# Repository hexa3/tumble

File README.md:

# tumble

its a dice but the pips act like real little discs. tilt it and they roll around, shake it and they bounce off the walls. when u stop shaking it picks a random number, the pips jump into that face and a motor goes thud.

it does d4, d6, d8, d10, d12, d20 and d100. double tap the face to switch.

tumble is the sequel to tinydie mk i (an attiny412 with 7 leds on a coin cell). when it turns on the pips start in the mk i's "7" pattern, and theres a gold outline of the old chip on the back cuz i love that little guy.

## whats inside

its 3 boards stacked up, 50x50mm each:

- **face**: 121 tiny leds in an 11x11 grid, run by an is31fl3733b
- **core**: the brain. an 8 pin stm32g041j6, a lis3dh accelerometer, a drv2605l with a buzzy motor, and an avalanche noise thing for randomness
- **base**: usb-c, battery charging, an mcp2221a for usb serial, a max17048 battery gauge and the battery

## is it actually fair

ya and u can check it urself. the noise goes through health tests (sp 800-90b) so it cant be stuck, then gets mixed into a blake2s pool that feeds chacha20, and the rolls come out of that. if the noise thing dies it switches to the chips own random generator and a little dot shows up in the corner.

plug it into usb and open serial at 115200:

```
raw N       dumps N raw noise samples
roll N S    rolls an S sided die N times, reseeding before each one
health      shows if the noise is ok
```

## building it

**firmware** (`firmware/`): its platformio. the so-8 chip isnt in platformio so theres my own board file in `boards/tumble_g041j6.json`. heads up: the debug pins turn into other stuff after boot, so u only have 2 seconds after reset to plug in a programmer.

**boards** (`hardware/`): run `build.sh`. it makes all 3 boards, runs drc (stops if anything fails), and spits out gerbers, boms, jlc files and pictures into `hardware/release/`. u need kicad 10 and the system python.

## what i still need to do

build it :)

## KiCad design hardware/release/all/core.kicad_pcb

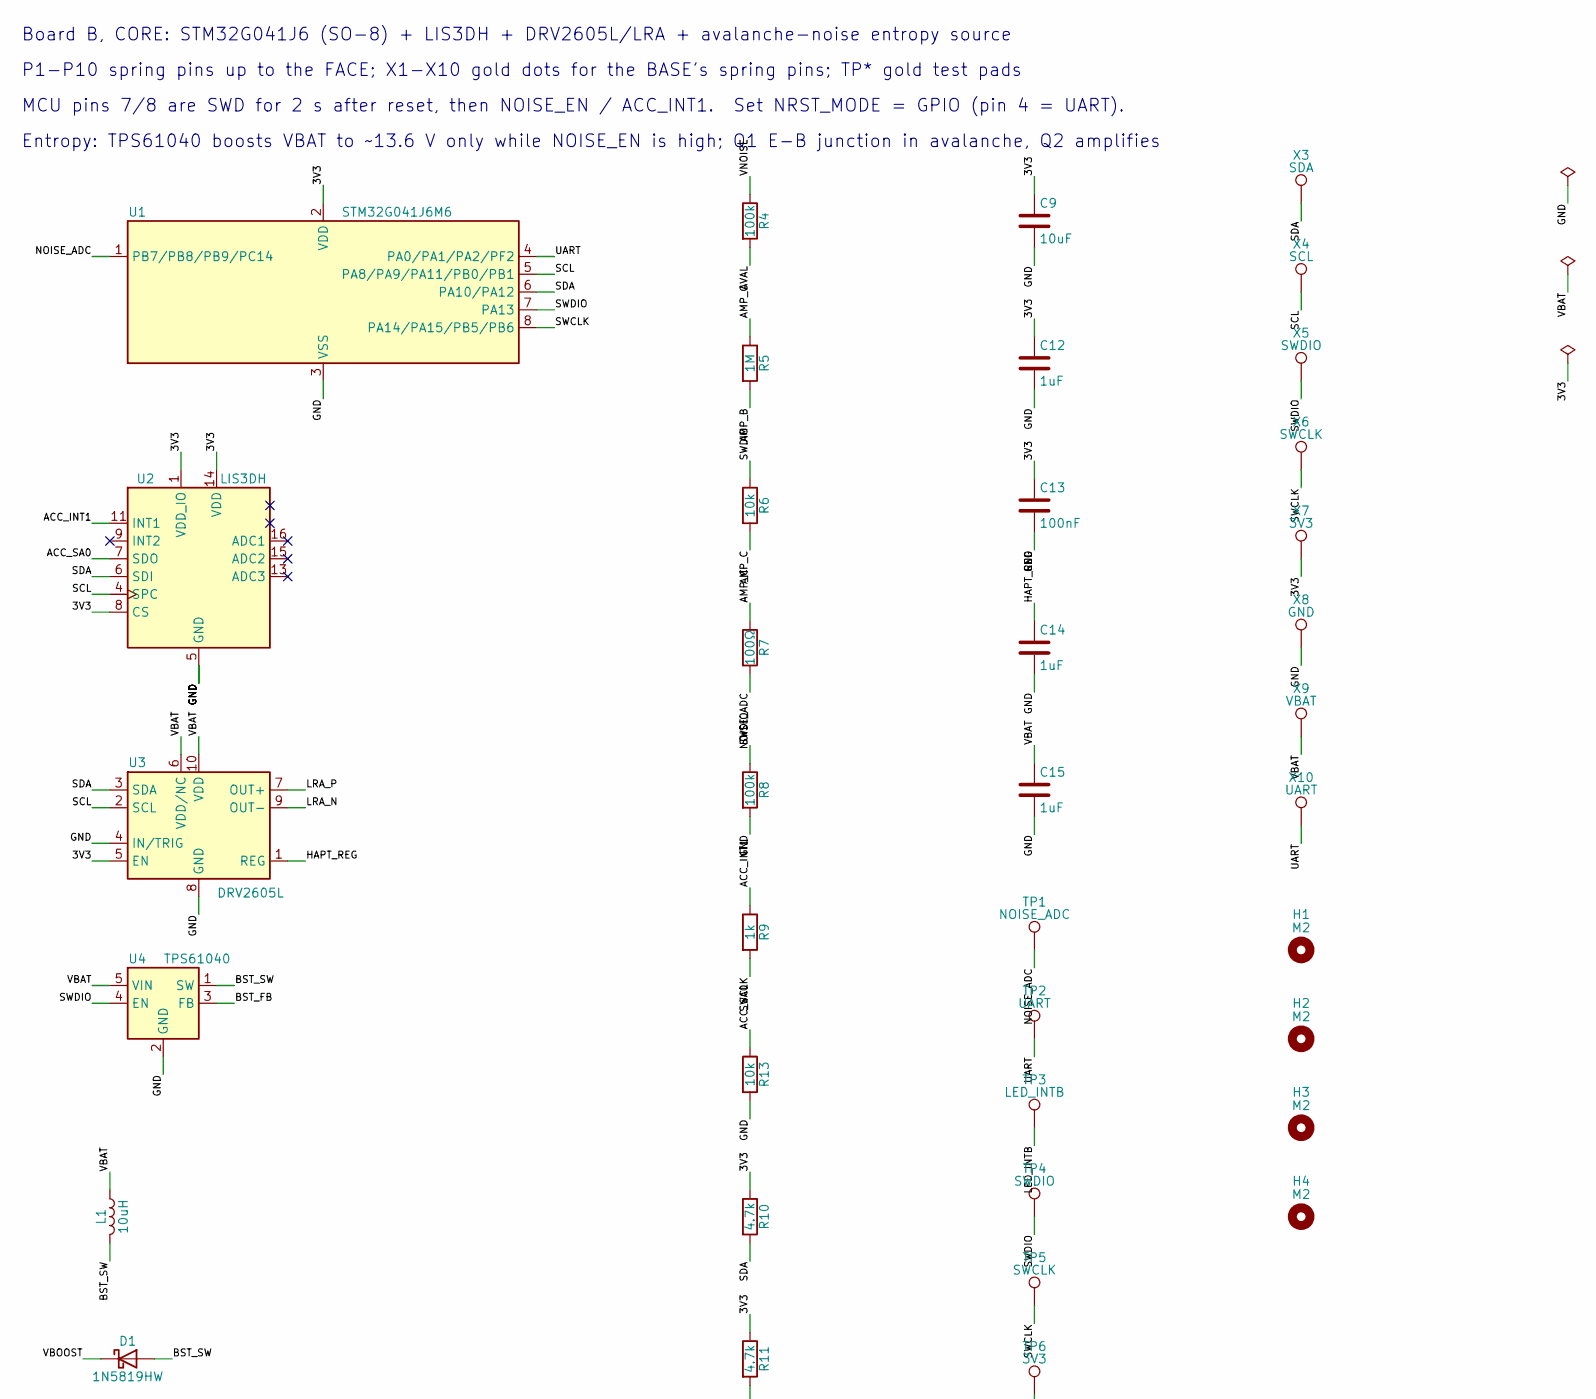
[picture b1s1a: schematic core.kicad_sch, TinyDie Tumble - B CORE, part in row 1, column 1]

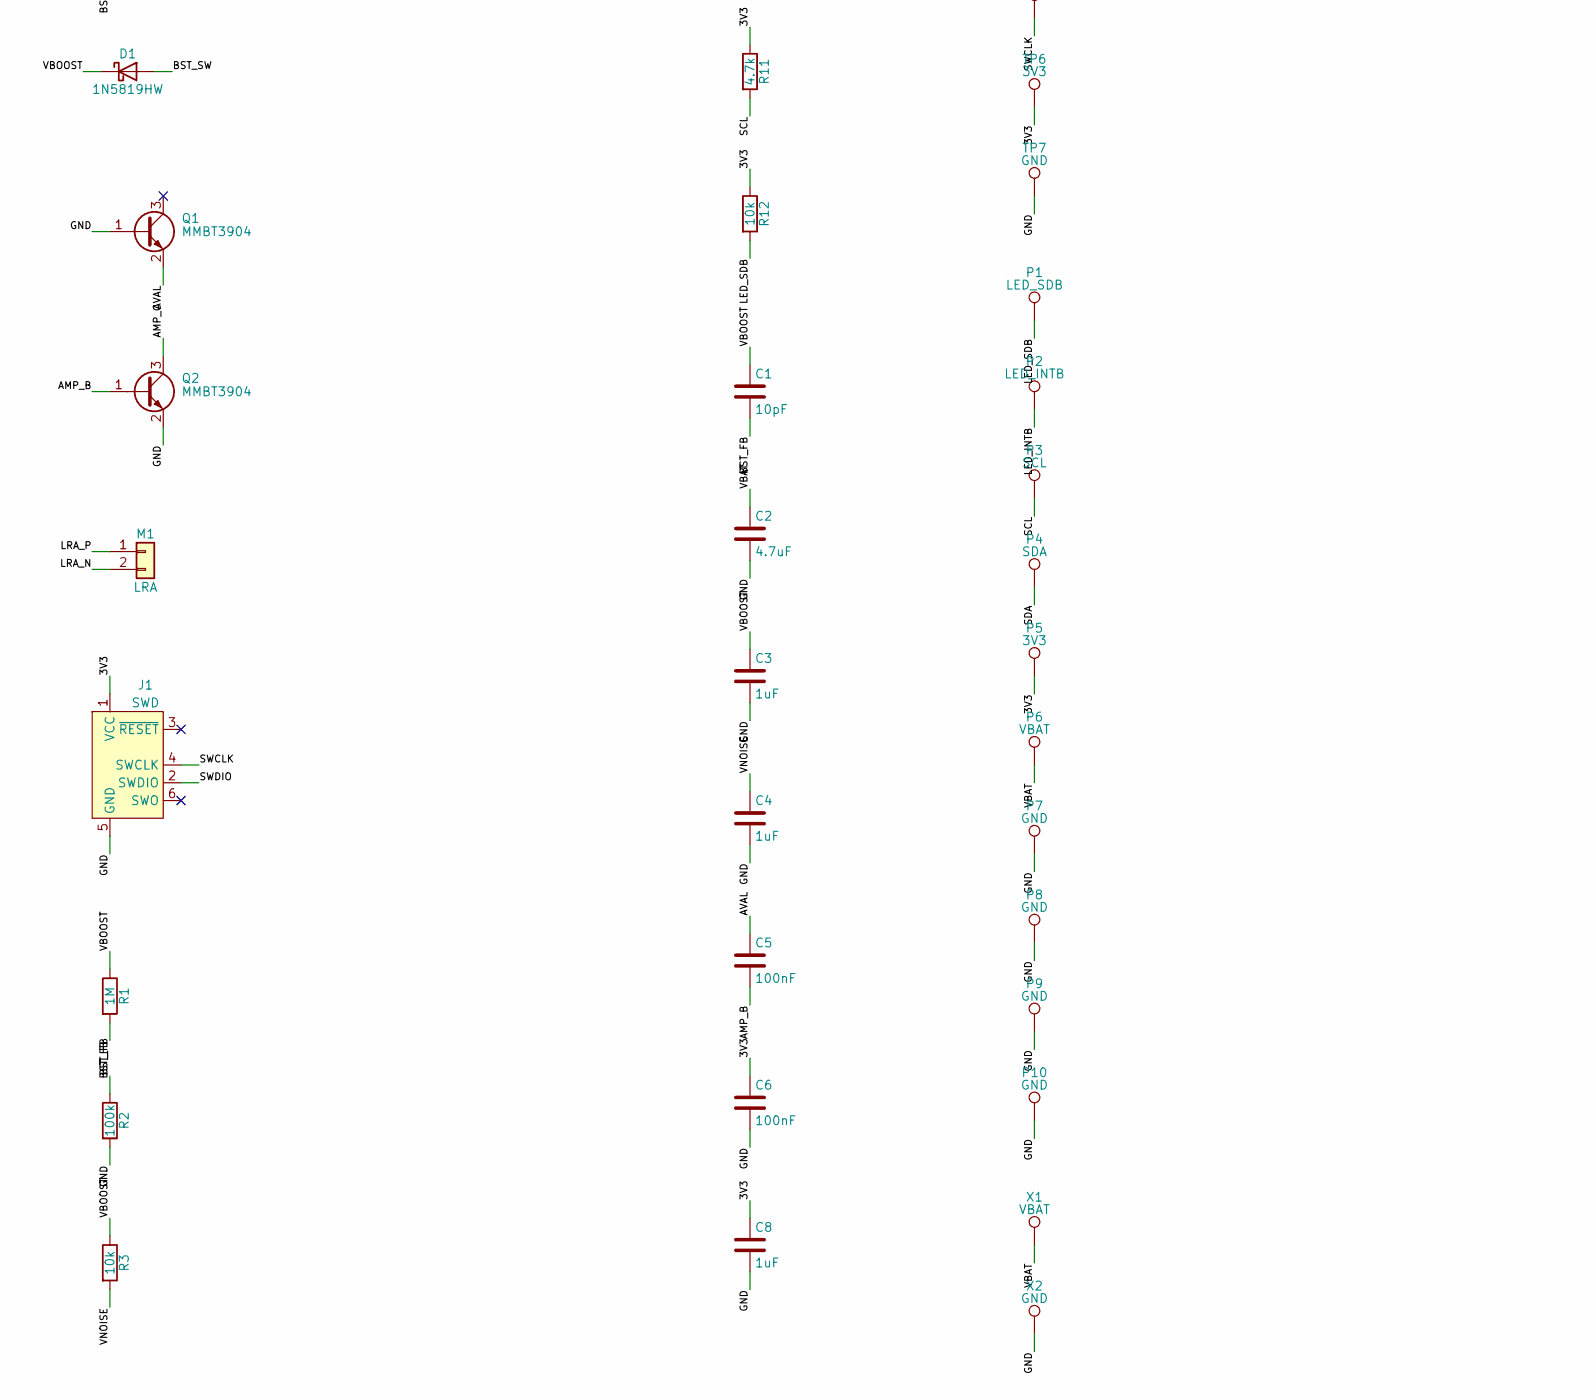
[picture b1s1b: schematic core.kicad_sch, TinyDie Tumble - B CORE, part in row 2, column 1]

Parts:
C1: 10pF; C_0402_1005Metric; MPN CL05C100JB5NNNC; DigiKey_PN TBD (verify)
C2: 4.7uF; C_0402_1005Metric; MPN C1005X5R1A475K050BC; DigiKey_PN 445-13820-1-ND
C3, C4, C8, C12, C14, C15: 1uF; C_0402_1005Metric; MPN CL05A105KA5NQNC; DigiKey_PN 1276-1445-1-ND
C5, C6, C13: 100nF; C_0402_1005Metric; MPN CL05B104KO5NNNC; DigiKey_PN 1276-1001-1-ND
C9: 10uF; C_0603_1608Metric; MPN LMK107BBJ106MALT; DigiKey_PN 587-3258-1-ND
D1: 1N5819HW; D_SOD-123; MPN 1N5819HW-7-F; DigiKey_PN 1N5819HW-FDICT-ND
H1, H2, H3, H4: M2; MountingHole_2.2mm_M2; MPN N/A (PCB copper feature, not a part); DigiKey_PN N/A
J1: SWD; Tag-Connect_TC2030-IDC-NL_2x03_P1.27mm_Vertical; MPN N/A (PCB copper feature, not a part); DigiKey_PN N/A
L1: 10uH; L_1210_3225Metric; MPN LQH32PH100MN0L; DigiKey_PN TBD (verify)
M1: LRA; LRA_Pads; MPN VG0832022D; DigiKey_PN 1670-VG0832022D-ND
P1: LED_SDB; Pogo_MillMax_0900-2; MPN 0900-2-15-20-75-14-11-0; DigiKey_PN ED9002-ND
P2: LED_INTB; Pogo_MillMax_0900-2; MPN 0900-2-15-20-75-14-11-0; DigiKey_PN ED9002-ND
P3: SCL; Pogo_MillMax_0900-2; MPN 0900-2-15-20-75-14-11-0; DigiKey_PN ED9002-ND
P4: SDA; Pogo_MillMax_0900-2; MPN 0900-2-15-20-75-14-11-0; DigiKey_PN ED9002-ND
P5: 3V3; Pogo_MillMax_0900-2; MPN 0900-2-15-20-75-14-11-0; DigiKey_PN ED9002-ND
P6: VBAT; Pogo_MillMax_0900-2; MPN 0900-2-15-20-75-14-11-0; DigiKey_PN ED9002-ND
P7, P8, P9, P10: GND; Pogo_MillMax_0900-2; MPN 0900-2-15-20-75-14-11-0; DigiKey_PN ED9002-ND
Q1, Q2: MMBT3904; SOT-23; MPN MMBT3904LT1G; DigiKey_PN TBD (verify)
R1, R5: 1M; R_0402_1005Metric; MPN RC0402FR-071ML; DigiKey_PN 311-1.00MLRCT-ND
R2, R4, R8: 100k; R_0402_1005Metric; MPN RC0402FR-07100KL; DigiKey_PN 311-100KLRCT-ND
R3, R6, R12, R13: 10k; R_0402_1005Metric; MPN RC0402FR-0710KL; DigiKey_PN 311-10.0KLRCT-ND
R7: 100Ω; R_0402_1005Metric; MPN RC0402FR-07100RL; DigiKey_PN 311-100LRCT-ND
R9: 1k; R_0402_1005Metric; MPN RC0402FR-071KL; DigiKey_PN 311-1.00KLRCT-ND
R10, R11: 4.7k; R_0402_1005Metric; MPN RC0402FR-074K7L; DigiKey_PN 311-4.70KLRCT-ND
TP1: NOISE_ADC; GoldDot_D1.5; MPN N/A (PCB copper feature, not a part); DigiKey_PN N/A
TP2: UART; GoldDot_D1.5; MPN N/A (PCB copper feature, not a part); DigiKey_PN N/A
TP3: LED_INTB; GoldDot_D1.5; MPN N/A (PCB copper feature, not a part); DigiKey_PN N/A
TP4: SWDIO; GoldDot_D1.5; MPN N/A (PCB copper feature, not a part); DigiKey_PN N/A
TP5: SWCLK; GoldDot_D1.5; MPN N/A (PCB copper feature, not a part); DigiKey_PN N/A
TP6: 3V3; GoldDot_D1.5; MPN N/A (PCB copper feature, not a part); DigiKey_PN N/A
TP7: GND; GoldDot_D1.5; MPN N/A (PCB copper feature, not a part); DigiKey_PN N/A
U1: STM32G041J6M6; SOIC-8_3.9x4.9mm_P1.27mm; MPN STM32G041J6M6; DigiKey_PN 497-STM32G041J6M6-ND
U2: LIS3DH; LGA-16_3x3mm_P0.5mm_FINE; MPN LIS3DHTR; DigiKey_PN 497-10613-1-ND
U3: DRV2605L; MSOP-10_3x3mm_P0.5mm_OSH; MPN DRV2605LDGSR; DigiKey_PN TBD (verify)
U4: TPS61040; SOT-23-5; MPN TPS61040DBVR; DigiKey_PN TBD (verify)
X1, X9: VBAT; PogoLand_D2.2; MPN N/A (PCB copper feature, not a part); DigiKey_PN N/A
X2, X8: GND; PogoLand_D2.2; MPN N/A (PCB copper feature, not a part); DigiKey_PN N/A
X3: SDA; PogoLand_D2.2; MPN N/A (PCB copper feature, not a part); DigiKey_PN N/A
X4: SCL; PogoLand_D2.2; MPN N/A (PCB copper feature, not a part); DigiKey_PN N/A
X5: SWDIO; PogoLand_D2.2; MPN N/A (PCB copper feature, not a part); DigiKey_PN N/A
X6: SWCLK; PogoLand_D2.2; MPN N/A (PCB copper feature, not a part); DigiKey_PN N/A
X7: 3V3; PogoLand_D2.2; MPN N/A (PCB copper feature, not a part); DigiKey_PN N/A
X10: UART; PogoLand_D2.2; MPN N/A (PCB copper feature, not a part); DigiKey_PN N/A

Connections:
/3V3: C6.1, C8.1, C9.1, C12.1, C13.1, J1.1 (VCC), P5.1, R10.1, R11.1, R12.1, TP6.1, U1.2 (VDD), U2.1 (VDD_IO), U2.8 (CS), U2.14 (VDD), U3.5 (EN), X7.1
/ACC_INT1: R9.1, U2.11 (INT1)
/ACC_SA0: R13.1, U2.7 (SDO)
/AMP_B: C5.2, Q2.1 (B), R5.2
/AMP_C: Q2.3 (C), R5.1, R6.2, R7.1
/AVAL: C5.1, Q1.2 (E), R4.2
/BST_FB: C1.2, R1.2, R2.1, U4.3 (FB)
/BST_SW: D1.2 (A), L1.2, U4.1 (SW)
/GND: C2.2, C3.2, C4.2, C6.2, C8.2, C9.2, C12.2, C13.2, C14.2, C15.2, J1.5 (GND), P7.1, P8.1, P9.1, P10.1, Q1.1 (B), Q2.2 (E), R2.2, R8.2, R13.2, TP7.1, U1.3 (VSS), U2.5 (GND), U2.10 (GND), U2.12 (GND), U3.4 (IN/TRIG), U3.8 (GND), U4.2 (GND), X2.1, X8.1
/HAPT_REG: C14.1, U3.1 (REG)
/LED_INTB: P2.1, TP3.1
/LED_SDB: P1.1, R12.2
/LRA_N: M1.2, U3.9 (OUT-)
/LRA_P: M1.1, U3.7 (OUT+)
/NOISE_ADC: R7.2, TP1.1, U1.1 (PB7/PB8/PB9/PC14)
/SCL: P3.1, R11.2, U1.5 (PA8/PA9/PA11/PB0/PB1), U2.4 (SPC), U3.2 (SCL), X4.1
/SDA: P4.1, R10.2, U1.6 (PA10/PA12), U2.6 (SDI), U3.3 (SDA), X3.1
/SWCLK: J1.4 (SWCLK), R9.2, TP5.1, U1.8 (PA14/PA15/PB5/PB6), X6.1
/SWDIO: J1.2 (SWDIO), R6.1, R8.1, TP4.1, U1.7 (PA13), U4.4 (EN), X5.1
/UART: TP2.1, U1.4 (PA0/PA1/PA2/PF2), X10.1
/VBAT: C2.1, C15.1, L1.1, P6.1, U3.6 (VDD/NC), U3.10 (VDD), U4.5 (VIN), X1.1, X9.1
/VBOOST: C1.1, C3.1, D1.1 (K), R1.1, R3.1
/VNOISE: C4.1, R3.2, R4.1

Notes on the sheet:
Board B, CORE: STM32G041J6 (SO-8) + LIS3DH + DRV2605L/LRA + avalanche-noise entropy source
P1-P10 spring pins up to the FACE; X1-X10 gold dots for the BASE's spring pins; TP* gold test pads
MCU pins 7/8 are SWD for 2 s after reset, then NOISE_EN / ACC_INT1. Set NRST_MODE = GPIO (pin 4 = UART).
Entropy: TPS61040 boosts VBAT to ~13.6 V only while NOISE_EN is high; Q1 E-B junction in avalanche, Q2 amplifies

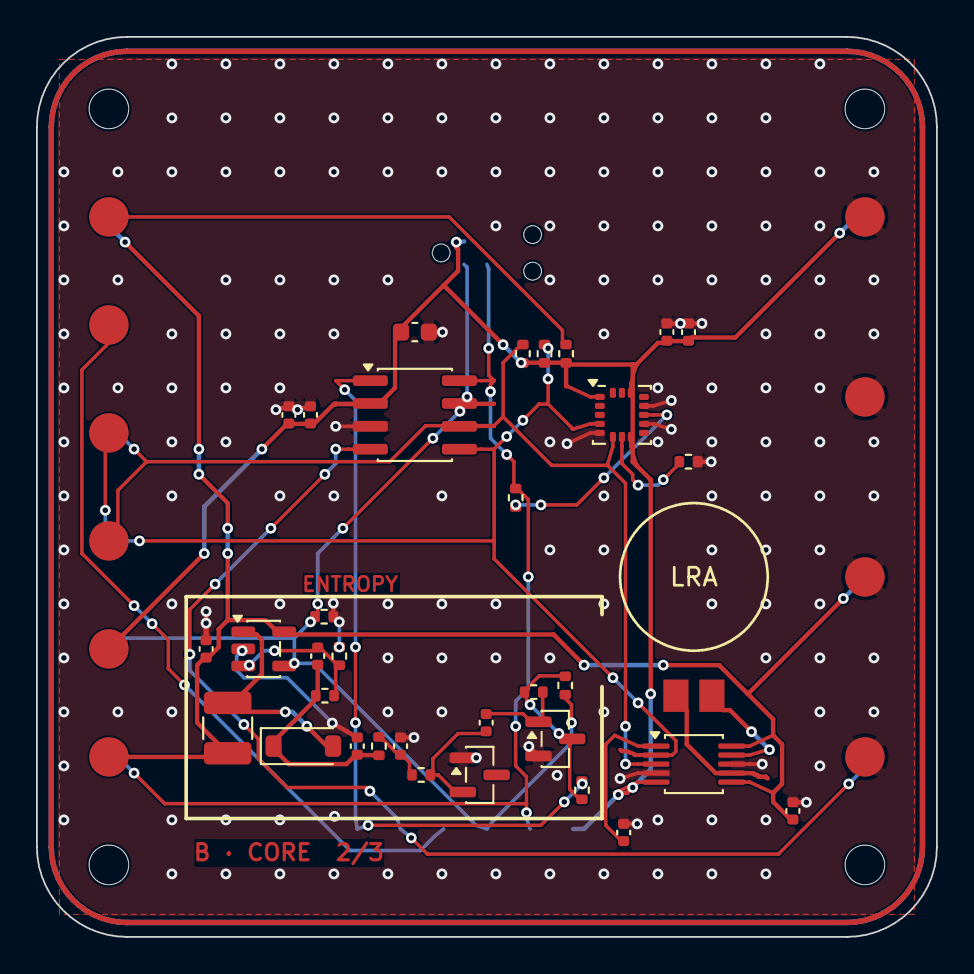
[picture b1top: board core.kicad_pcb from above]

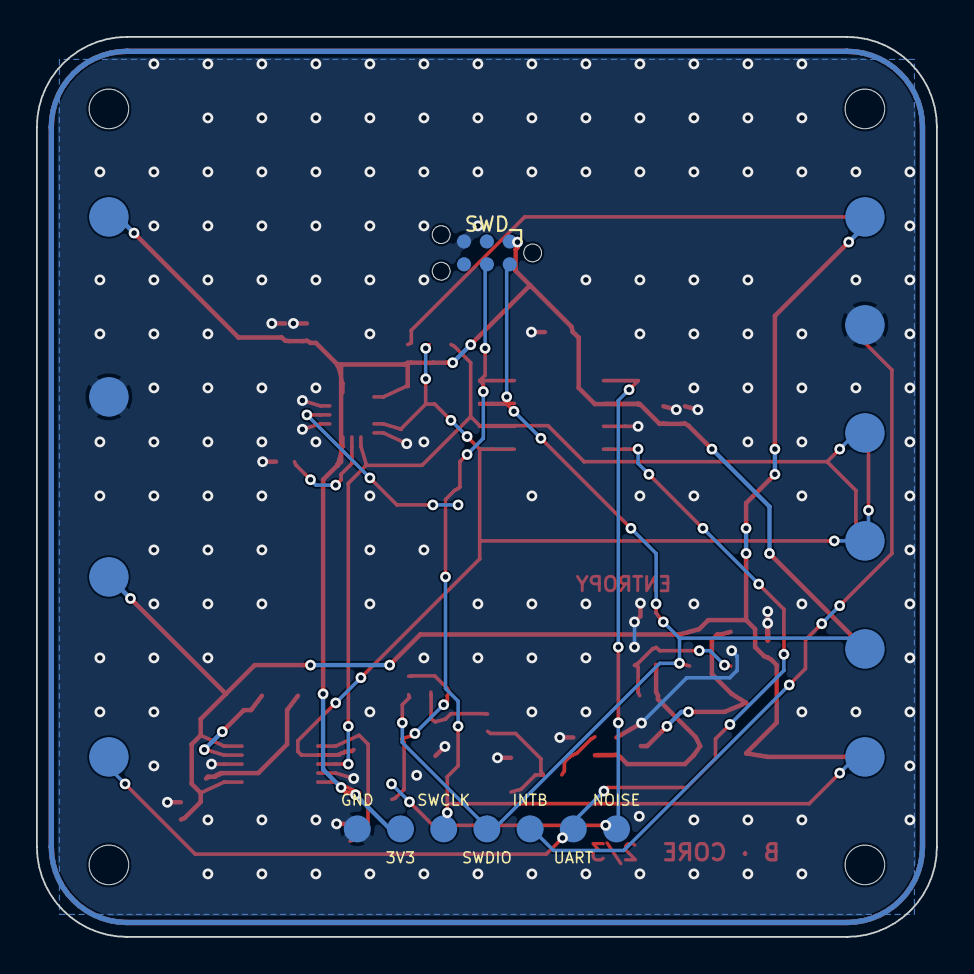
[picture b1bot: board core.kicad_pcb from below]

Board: 2 copper layers, 50.0 x 50.0 mm, 66 parts (18 on the bottom side), 23 nets.

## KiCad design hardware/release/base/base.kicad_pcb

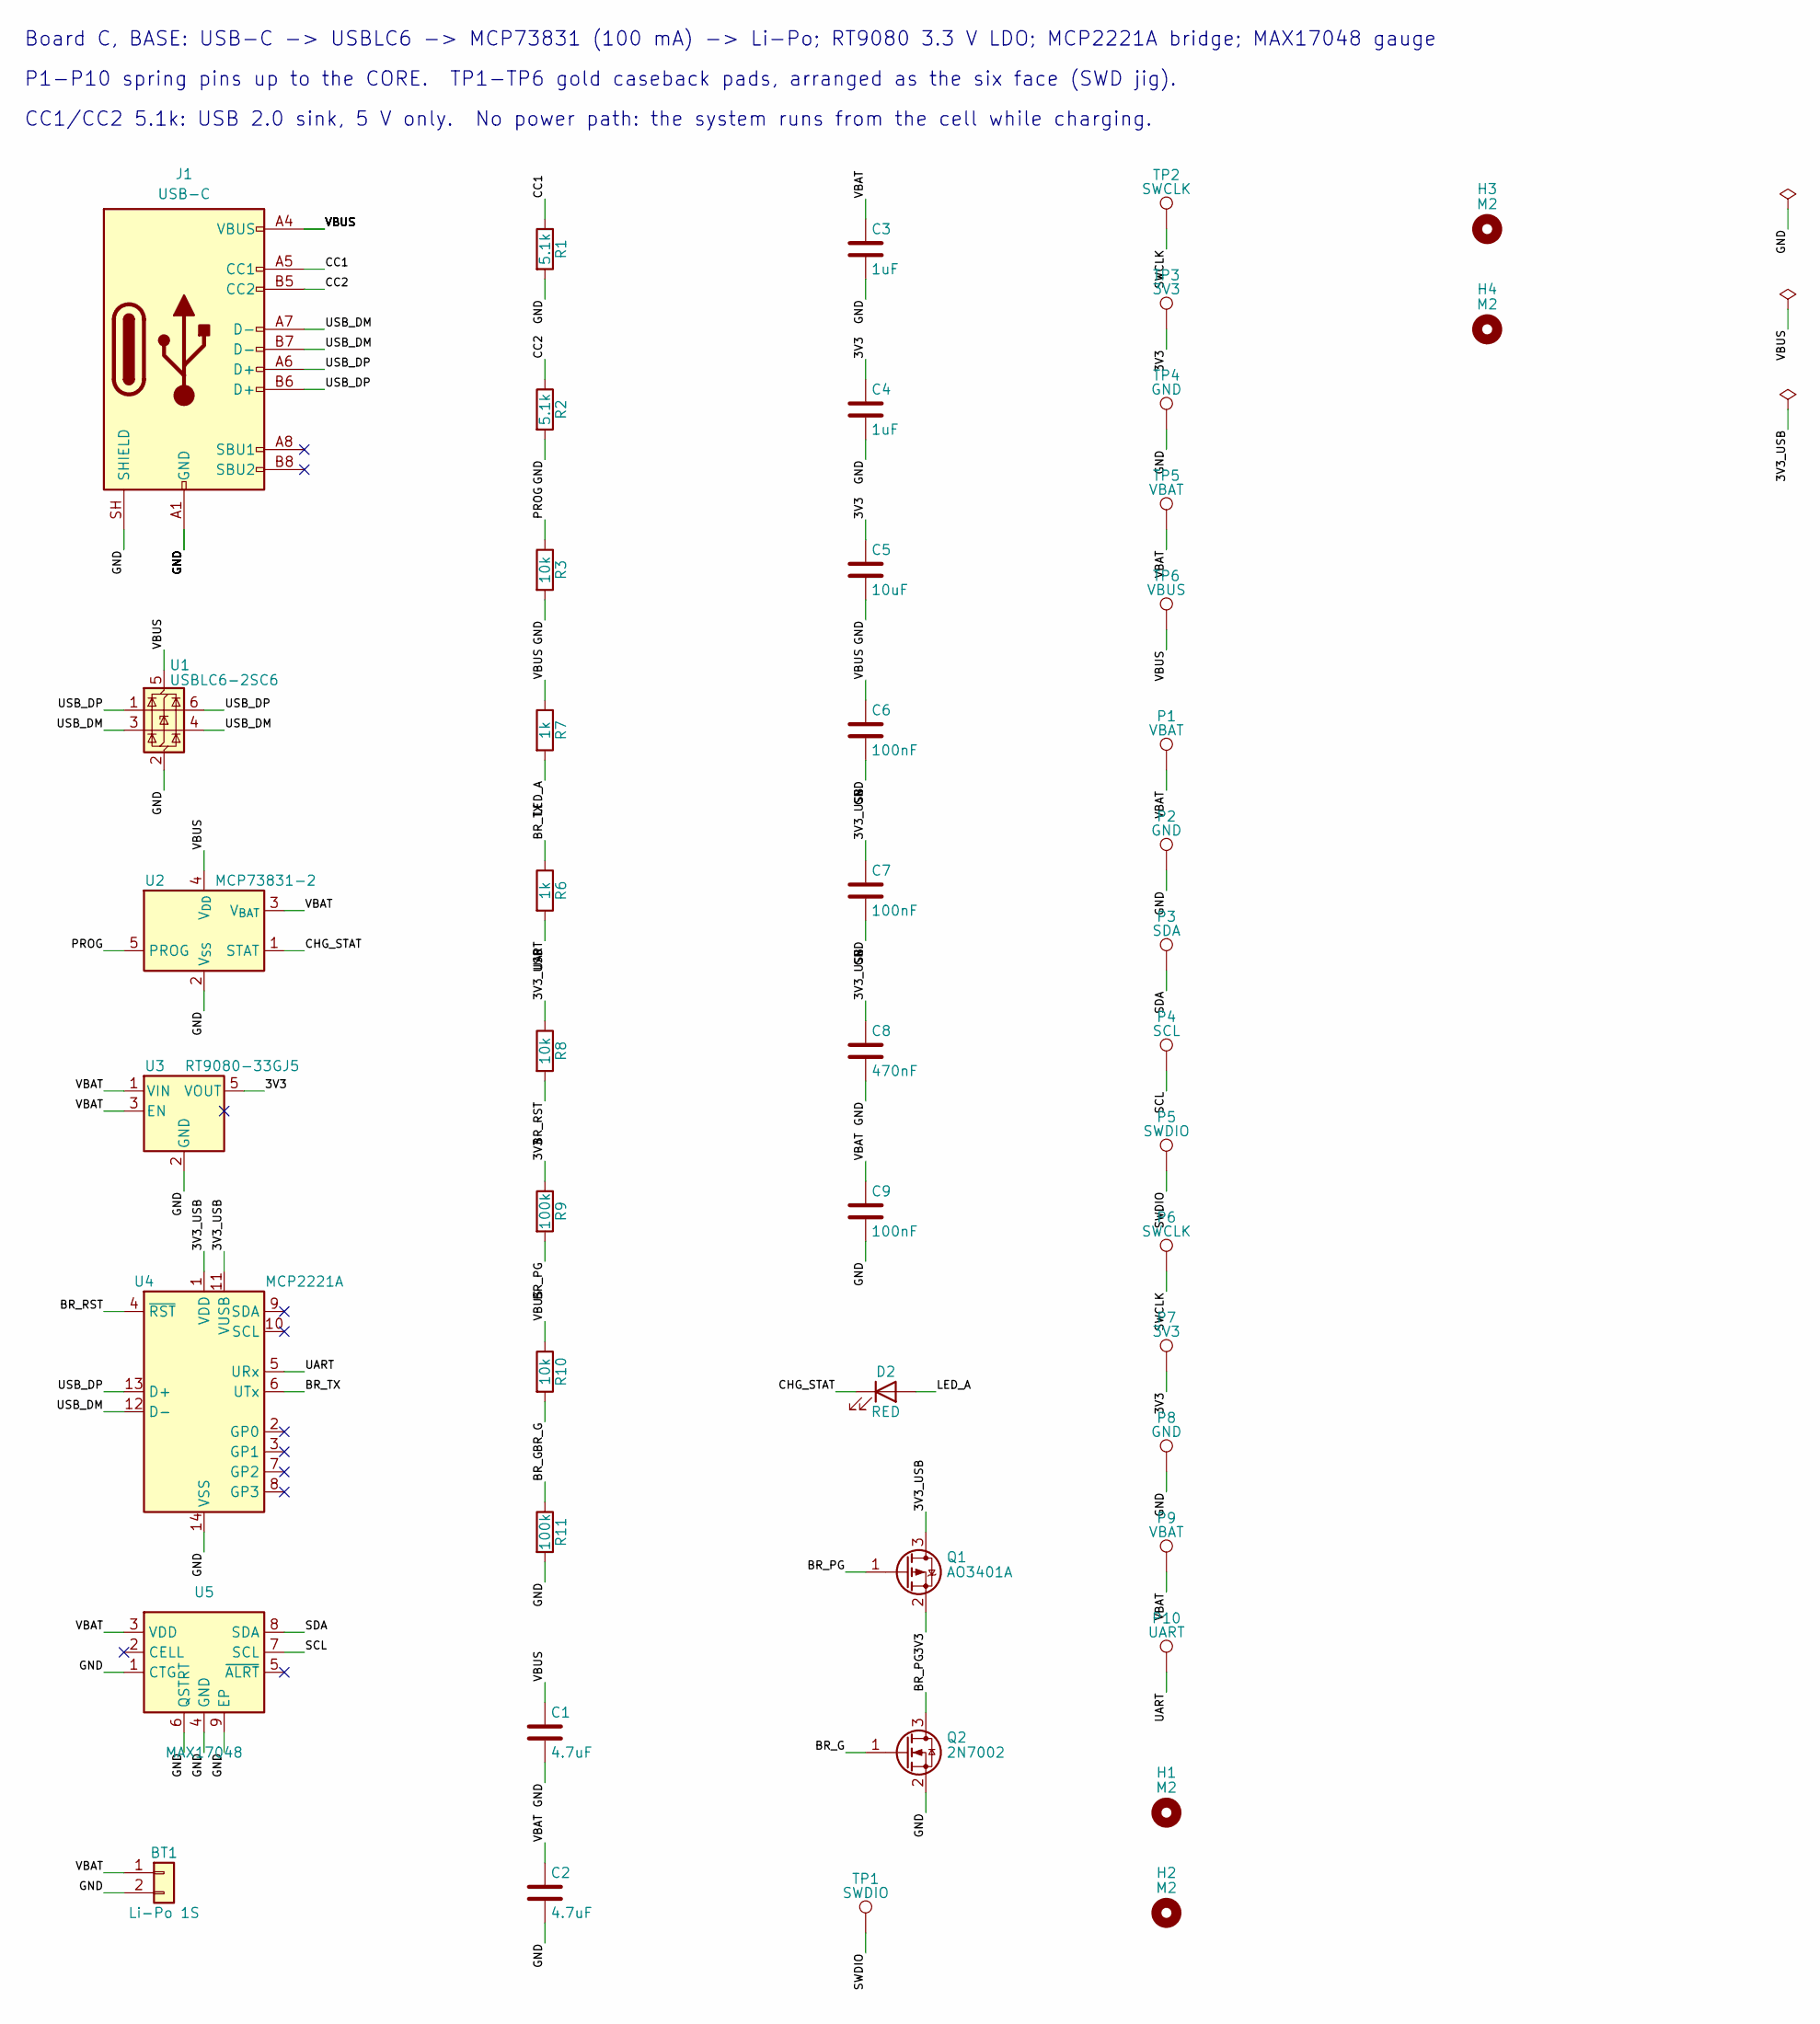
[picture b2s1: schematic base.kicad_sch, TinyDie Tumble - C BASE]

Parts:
BT1: Li-Po 1S; BatteryPads_2x2.2x2.8; MPN TBD (1S Li-Po with protection, <= 34 x 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; DigiKey_PN TBD (verify)
C1, C2: 4.7uF; C_0402_1005Metric; MPN C1005X5R1A475K050BC; DigiKey_PN 445-13820-1-ND
C3, C4: 1uF; C_0402_1005Metric; MPN CL05A105KA5NQNC; DigiKey_PN 1276-1445-1-ND
C5: 10uF; C_0603_1608Metric; MPN LMK107BBJ106MALT; DigiKey_PN 587-3258-1-ND
C6, C7, C9: 100nF; C_0402_1005Metric; MPN CL05B104KO5NNNC; DigiKey_PN 1276-1001-1-ND
C8: 470nF; C_0402_1005Metric; MPN CL05A474KO5NNNC; DigiKey_PN TBD (verify)
D2: RED; LED_0603_1608Metric; MPN LTST-C191KRKT; DigiKey_PN 160-1447-1-ND
H1, H2, H3, H4: M2; MountingHole_2.2mm_M2; MPN N/A (PCB copper feature, not a part); DigiKey_PN N/A
J1: USB-C; USB_C_Receptacle_GCT_USB4105-xx-A_16P_TopMnt_Horizontal; MPN USB4105-GF-A; DigiKey_PN 2073-USB4105-GF-ACT-ND
P1, P9: VBAT; Pogo_MillMax_0900-2; MPN 0900-2-15-20-75-14-11-0; DigiKey_PN ED9002-ND
P2, P8: GND; Pogo_MillMax_0900-2; MPN 0900-2-15-20-75-14-11-0; DigiKey_PN ED9002-ND
P3: SDA; Pogo_MillMax_0900-2; MPN 0900-2-15-20-75-14-11-0; DigiKey_PN ED9002-ND
P4: SCL; Pogo_MillMax_0900-2; MPN 0900-2-15-20-75-14-11-0; DigiKey_PN ED9002-ND
P5: SWDIO; Pogo_MillMax_0900-2; MPN 0900-2-15-20-75-14-11-0; DigiKey_PN ED9002-ND
P6: SWCLK; Pogo_MillMax_0900-2; MPN 0900-2-15-20-75-14-11-0; DigiKey_PN ED9002-ND
P7: 3V3; Pogo_MillMax_0900-2; MPN 0900-2-15-20-75-14-11-0; DigiKey_PN ED9002-ND
P10: UART; Pogo_MillMax_0900-2; MPN 0900-2-15-20-75-14-11-0; DigiKey_PN ED9002-ND
Q1: AO3401A; SOT-23; MPN AO3401A; DigiKey_PN 785-1001-1-ND
Q2: 2N7002; SOT-23; MPN 2N7002LT1G; DigiKey_PN 2N7002LT1GOSCT-ND
R1, R2: 5.1k; R_0402_1005Metric; MPN RC0402FR-075K1L; DigiKey_PN 311-5.10KLRCT-ND
R3, R8, R10: 10k; R_0402_1005Metric; MPN RC0402FR-0710KL; DigiKey_PN 311-10.0KLRCT-ND
R6, R7: 1k; R_0402_1005Metric; MPN RC0402FR-071KL; DigiKey_PN 311-1.00KLRCT-ND
R9, R11: 100k; R_0402_1005Metric; MPN RC0402FR-07100KL; DigiKey_PN 311-100KLRCT-ND
TP1: SWDIO; GoldDot_D3.0; MPN N/A (PCB copper feature, not a part); DigiKey_PN N/A
TP2: SWCLK; GoldDot_D3.0; MPN N/A (PCB copper feature, not a part); DigiKey_PN N/A
TP3: 3V3; GoldDot_D3.0; MPN N/A (PCB copper feature, not a part); DigiKey_PN N/A
TP4: GND; GoldDot_D3.0; MPN N/A (PCB copper feature, not a part); DigiKey_PN N/A
TP5: VBAT; GoldDot_D3.0; MPN N/A (PCB copper feature, not a part); DigiKey_PN N/A
TP6: VBUS; GoldDot_D3.0; MPN N/A (PCB copper feature, not a part); DigiKey_PN N/A
U1: USBLC6-2SC6; SOT-23-6; MPN USBLC6-2SC6; DigiKey_PN 497-5235-1-ND
U2: MCP73831-2; SOT-23-5; MPN MCP73831T-2ACI/OT; DigiKey_PN MCP73831T-2ACI/OTCT-ND
U3: RT9080-33GJ5; SOT-23-5; MPN RT9080-33GJ5; DigiKey_PN 1028-1509-1-ND
U4: MCP2221A; SOIC-14_3.9x8.7mm_P1.27mm; MPN MCP2221A-I/SL; DigiKey_PN MCP2221A-I/SL-ND
U5: MAX17048; DFN-8-1EP_2x2mm_P0.5mm_EP0.8x1.6mm; MPN MAX17048G+T10; DigiKey_PN TBD (verify)

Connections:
/3V3: C4.1, C5.1, P7.1, Q1.2 (S), R9.1, TP3.1, U3.5 (VOUT)
/3V3_USB: C7.1, C8.1, Q1.3 (D), R8.1, U4.1 (VDD), U4.11 (VUSB)
/BR_G: Q2.1 (G), R10.2, R11.1
/BR_PG: Q1.1 (G), Q2.3 (D), R9.2
/BR_RST: R8.2, U4.4 (~RST)
/BR_TX: R6.1, U4.6 (UTx)
/CC1: J1.A5 (CC1), R1.1
/CC2: J1.B5 (CC2), R2.1
/CHG_STAT: D2.1 (K), U2.1 (STAT)
/GND: BT1.2, C1.2, C2.2, C3.2, C4.2, C5.2, C6.2, C7.2, C8.2, C9.2, J1.A1 (GND), J1.A12 (GND), J1.B1 (GND), J1.B12 (GND), J1.SH (SHIELD), P2.1, P8.1, Q2.2 (S), R1.2, R2.2, R3.2, R11.2, TP4.1, U1.2 (GND), U2.2 (V_{SS}), U3.2 (GND), U4.14 (VSS), U5.1 (CTG), U5.4 (GND), U5.6 (QSTRT), U5.9 (EP)
/LED_A: D2.2 (A), R7.2
/PROG: R3.1, U2.5 (PROG)
/SCL: P4.1, U5.7 (SCL)
/SDA: P3.1, U5.8 (SDA)
/SWCLK: P6.1, TP2.1
/SWDIO: P5.1, TP1.1
/UART: P10.1, R6.2, U4.5 (URx)
/USB_DM: J1.A7 (D-), J1.B7 (D-), U1.3 (I/O2), U1.4 (I/O2), U4.12 (D-)
/USB_DP: J1.A6 (D+), J1.B6 (D+), U1.1 (I/O1), U1.6 (I/O1), U4.13 (D+)
/VBAT: BT1.1, C2.1, C3.1, C9.1, P1.1, P9.1, TP5.1, U2.3 (V_{BAT}), U3.1 (VIN), U3.3 (EN), U5.3 (VDD)
/VBUS: C1.1, C6.1, J1.A4 (VBUS), J1.A9 (VBUS), J1.B4 (VBUS), J1.B9 (VBUS), R7.1, R10.1, TP6.1, U1.5 (VBUS), U2.4 (V_{DD})

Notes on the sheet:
Board C, BASE: USB-C -> USBLC6 -> MCP73831 (100 mA) -> Li-Po; RT9080 3.3 V LDO; MCP2221A bridge; MAX17048 gauge
P1-P10 spring pins up to the CORE. TP1-TP6 gold caseback pads, arranged as the six face (SWD jig).
CC1/CC2 5.1k: USB 2.0 sink, 5 V only. No power path: the system runs from the cell while charging.

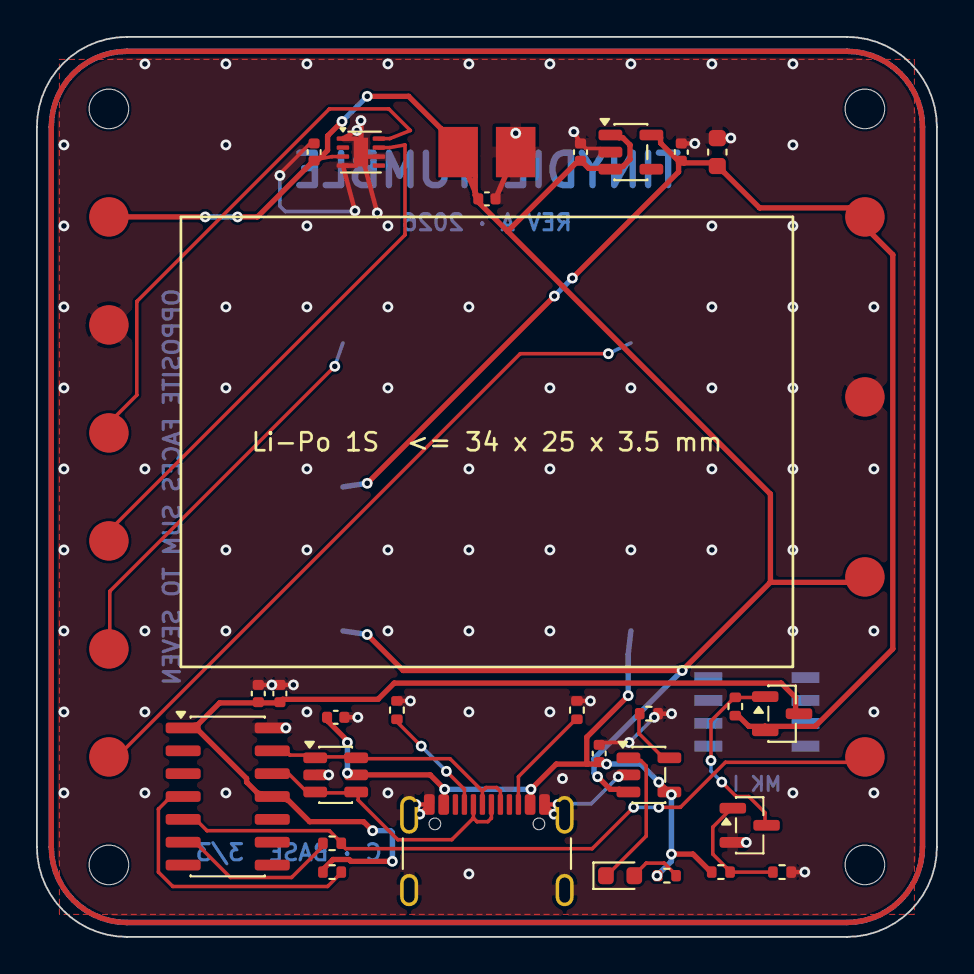
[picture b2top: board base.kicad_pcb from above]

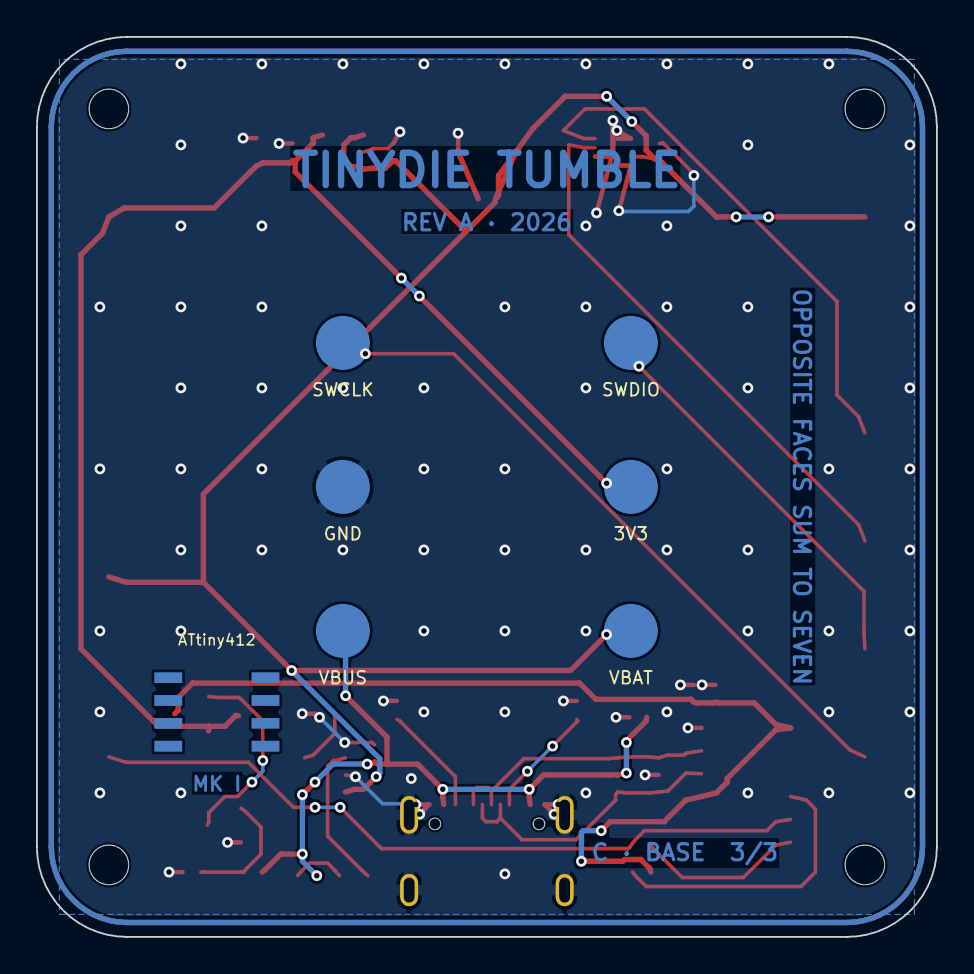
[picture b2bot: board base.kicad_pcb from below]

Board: 2 copper layers, 50.0 x 50.0 mm, 48 parts (6 on the bottom side), 21 nets.
